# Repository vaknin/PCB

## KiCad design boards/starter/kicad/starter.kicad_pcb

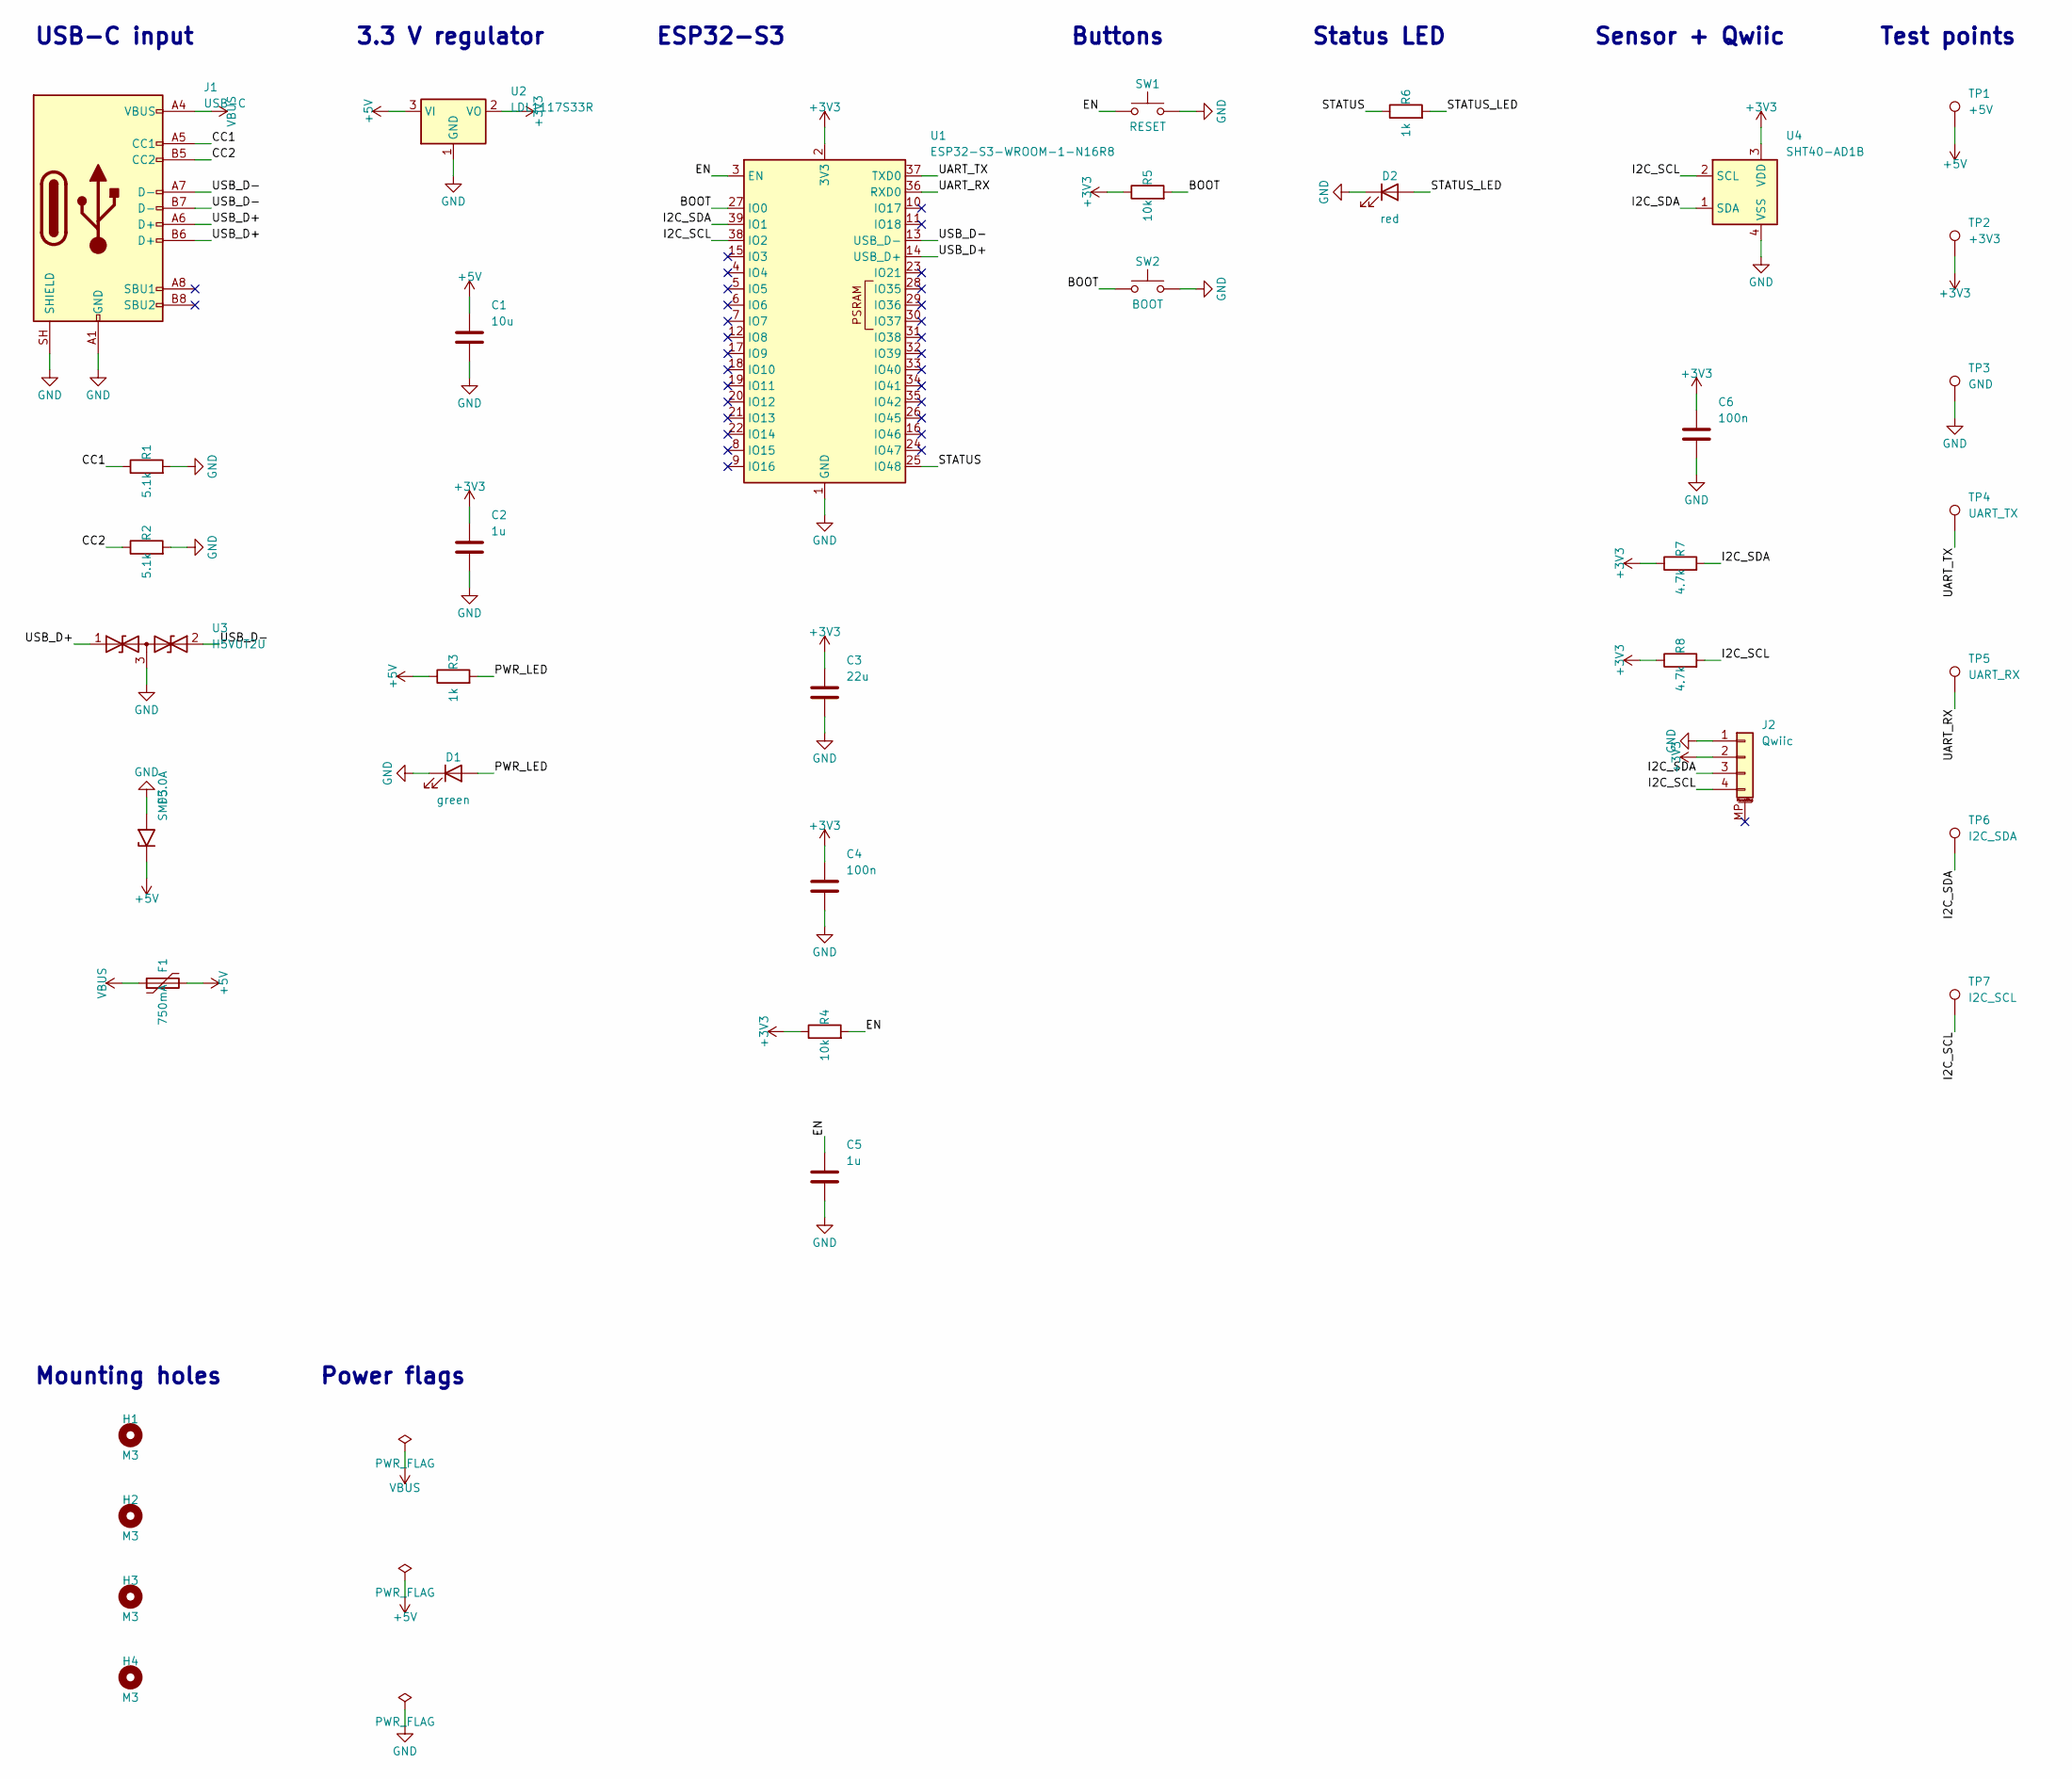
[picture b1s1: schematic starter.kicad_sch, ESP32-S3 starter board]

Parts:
C1: 10u; C_0805_2012Metric; MPN CL21A106KAYNNNE; LCSC C15850
C2, C5: 1u; C_0805_2012Metric; MPN CL21B105KBFNNNE; LCSC C28323
C3: 22u; C_0805_2012Metric; MPN CL21A226MAQNNNE; LCSC C45783
C4, C6: 100n; C_0805_2012Metric; MPN CC0805KRX7R9BB104; LCSC C49678
D1: green; LED_0805_2012Metric; MPN KT-0805G; LCSC C2297
D2: red; LED_0805_2012Metric; MPN NCD0805R1; LCSC C84256
D3: SMF5.0A; D_SOD-123F; MPN SMF5.0A; LCSC C19077497
F1: 750mA; Fuse_1206_3216Metric; MPN MF-NSMF075-2; LCSC C89653
H1, H2, H3, H4: M3; MountingHole_3.2mm_M3
J1: USB-C; USB_C_Receptacle_HRO_TYPE-C-31-M-12; MPN TYPE-C-31-M-12; LCSC C165948
J2: Qwiic; JST_SH_SM04B-SRSS-TB_1x04-1MP_P1.00mm_Horizontal; MPN SM04B-SRSS-TB; LCSC C160404
R1, R2: 5.1k; R_0805_2012Metric; MPN 0805W8F5101T5E; LCSC C27834
R3, R6: 1k; R_0805_2012Metric; MPN 0805W8F1001T5E; LCSC C17513
R4, R5: 10k; R_0805_2012Metric; MPN 0805W8F1002T5E; LCSC C17414
R7, R8: 4.7k; R_0805_2012Metric; MPN 0805W8F4701T5E; LCSC C17673
SW1: RESET; SW_Push_1P1T_XKB_TS-1187A; MPN TS-1187A-B-A-B; LCSC C318884
SW2: BOOT; SW_Push_1P1T_XKB_TS-1187A; MPN TS-1187A-B-A-B; LCSC C318884
TP1: +5V; TestPoint_Pad_D1.5mm
TP2: +3V3; TestPoint_Pad_D1.5mm
TP3: GND; TestPoint_Pad_D1.5mm
TP4: UART_TX; TestPoint_Pad_D1.5mm
TP5: UART_RX; TestPoint_Pad_D1.5mm
TP6: I2C_SDA; TestPoint_Pad_D1.5mm
TP7: I2C_SCL; TestPoint_Pad_D1.5mm
U1: ESP32-S3-WROOM-1-N16R8; ESP32-S3-WROOM-1_EPAD-Drill0.3; MPN ESP32-S3-WROOM-1-N16R8; LCSC C2913202
U2: LDL1117S33R; SOT-223-3_TabPin2; MPN LDL1117S33R; LCSC C435835
U3: H5VUT2U; SOT-23; MPN H5VUT2U; LCSC C20615824
U4: SHT40-AD1B; Sensirion_DFN-4_1.5x1.5mm_P0.8mm_SHT4x_NoCentralPad; MPN SHT40-AD1B-R2; LCSC C2909890

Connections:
+3V3: C2.1, C3.1, C4.1, C6.1, J2.2, R4.1, R5.1, R7.1, R8.1, TP2.1, U1.2 (3V3), U2.2 (VO), U4.3 (VDD)
+5V: C1.1, D3.1 (A1), F1.2, R3.1, TP1.1, U2.3 (VI)
/BOOT: R5.2, SW2.1, U1.27 (IO0)
/CC1: J1.A5 (CC1), R1.1
/CC2: J1.B5 (CC2), R2.1
/EN: C5.1, R4.2, SW1.1, U1.3 (EN)
/I2C_SCL: J2.4, R8.2, TP7.1, U1.38 (IO2), U4.2 (SCL)
/I2C_SDA: J2.3, R7.2, TP6.1, U1.39 (IO1), U4.1 (SDA)
/PWR_LED: D1.2 (A), R3.2
/STATUS: R6.1, U1.25 (IO48)
/STATUS_LED: D2.2 (A), R6.2
/UART_RX: TP5.1, U1.36 (RXD0)
/UART_TX: TP4.1, U1.37 (TXD0)
/USB_D+: J1.A6 (D+), J1.B6 (D+), U1.14 (USB_D+), U3.1 (A1)
/USB_D-: J1.A7 (D-), J1.B7 (D-), U1.13 (USB_D-), U3.2 (A2)
GND: C1.2, C2.2, C3.2, C4.2, C5.2, C6.2, D1.1 (K), D2.1 (K), D3.2 (A2), J1.A1 (GND), J1.A12 (GND), J1.B1 (GND), J1.B12 (GND), J1.SH (SHIELD), J2.1, R1.2, R2.2, SW1.2, SW2.2, TP3.1, U1.1 (GND), U1.40 (GND), U1.41 (GND), U2.1 (GND), U3.3 (common), U4.4 (VSS)
VBUS: F1.1, J1.A4 (VBUS), J1.A9 (VBUS), J1.B4 (VBUS), J1.B9 (VBUS)

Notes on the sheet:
Mounting holes
Sensor + Qwiic
ESP32-S3
USB-C input
Power flags
Buttons
Test points
3.3 V regulator
Status LED

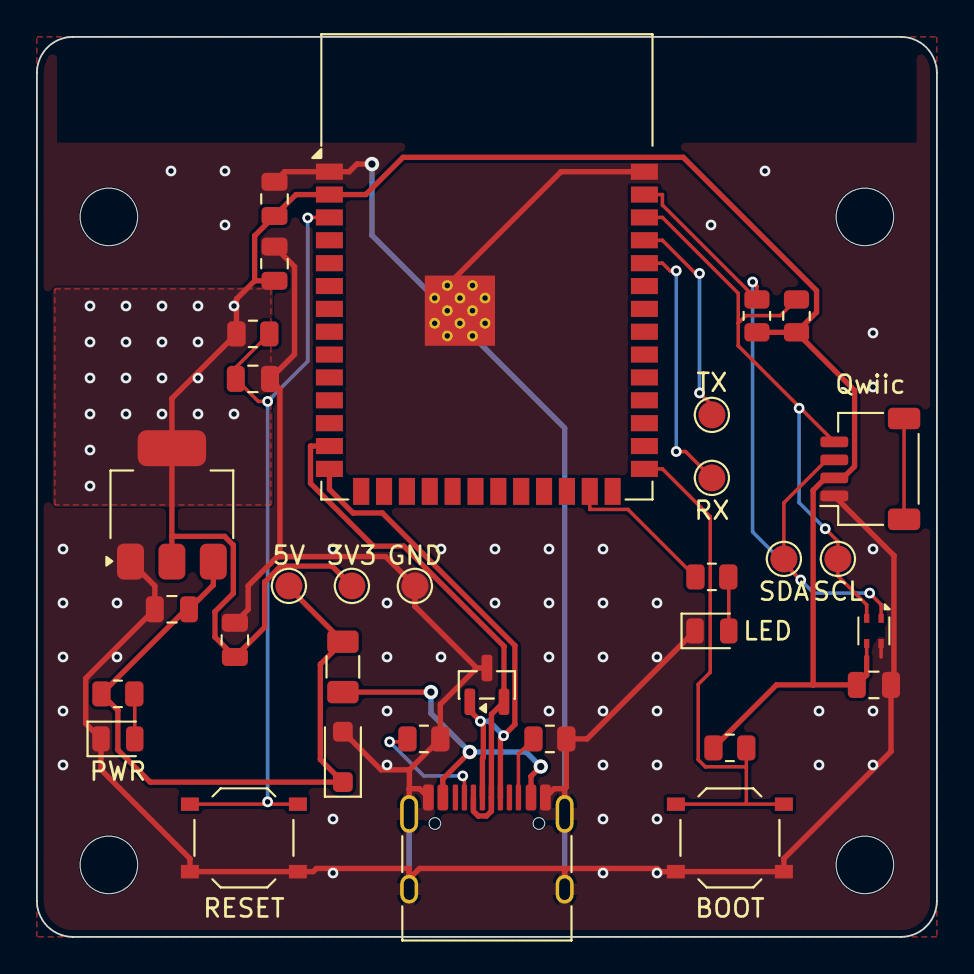
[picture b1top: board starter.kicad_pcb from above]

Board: 2 copper layers, 50.0 x 50.0 mm, 37 parts (0 on the bottom side), 17 nets.

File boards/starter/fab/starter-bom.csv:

Comment,Designator,Footprint,LCSC
10u,C1,C_0805_2012Metric,C15850
1u,"C2,C5",C_0805_2012Metric,C28323
22u,C3,C_0805_2012Metric,C45783
100n,"C4,C6",C_0805_2012Metric,C49678
green,D1,LED_0805_2012Metric,C2297
red,D2,LED_0805_2012Metric,C84256
SMF5.0A,D3,D_SOD-123F,C19077497
750mA,F1,Fuse_1206_3216Metric,C89653
USB-C,J1,USB_C_Receptacle_HRO_TYPE-C-31-M-12,C165948
Qwiic,J2,JST_SH_SM04B-SRSS-TB_1x04-1MP_P1.00mm_Horizontal,C160404
5.1k,"R1,R2",R_0805_2012Metric,C27834
1k,"R3,R6",R_0805_2012Metric,C17513
10k,"R4,R5",R_0805_2012Metric,C17414
4.7k,"R7,R8",R_0805_2012Metric,C17673
RESET,SW1,SW_Push_1P1T_XKB_TS-1187A,C318884
BOOT,SW2,SW_Push_1P1T_XKB_TS-1187A,C318884
ESP32-S3-WROOM-1-N16R8,U1,ESP32-S3-WROOM-1_EPAD-Drill0.3,C2913202
LDL1117S33R,U2,SOT-223-3_TabPin2,C435835
H5VUT2U,U3,SOT-23,C20615824
SHT40-AD1B,U4,Sensirion_DFN-4_1.5x1.5mm_P0.8mm_SHT4x_NoCentralPad,C2909890

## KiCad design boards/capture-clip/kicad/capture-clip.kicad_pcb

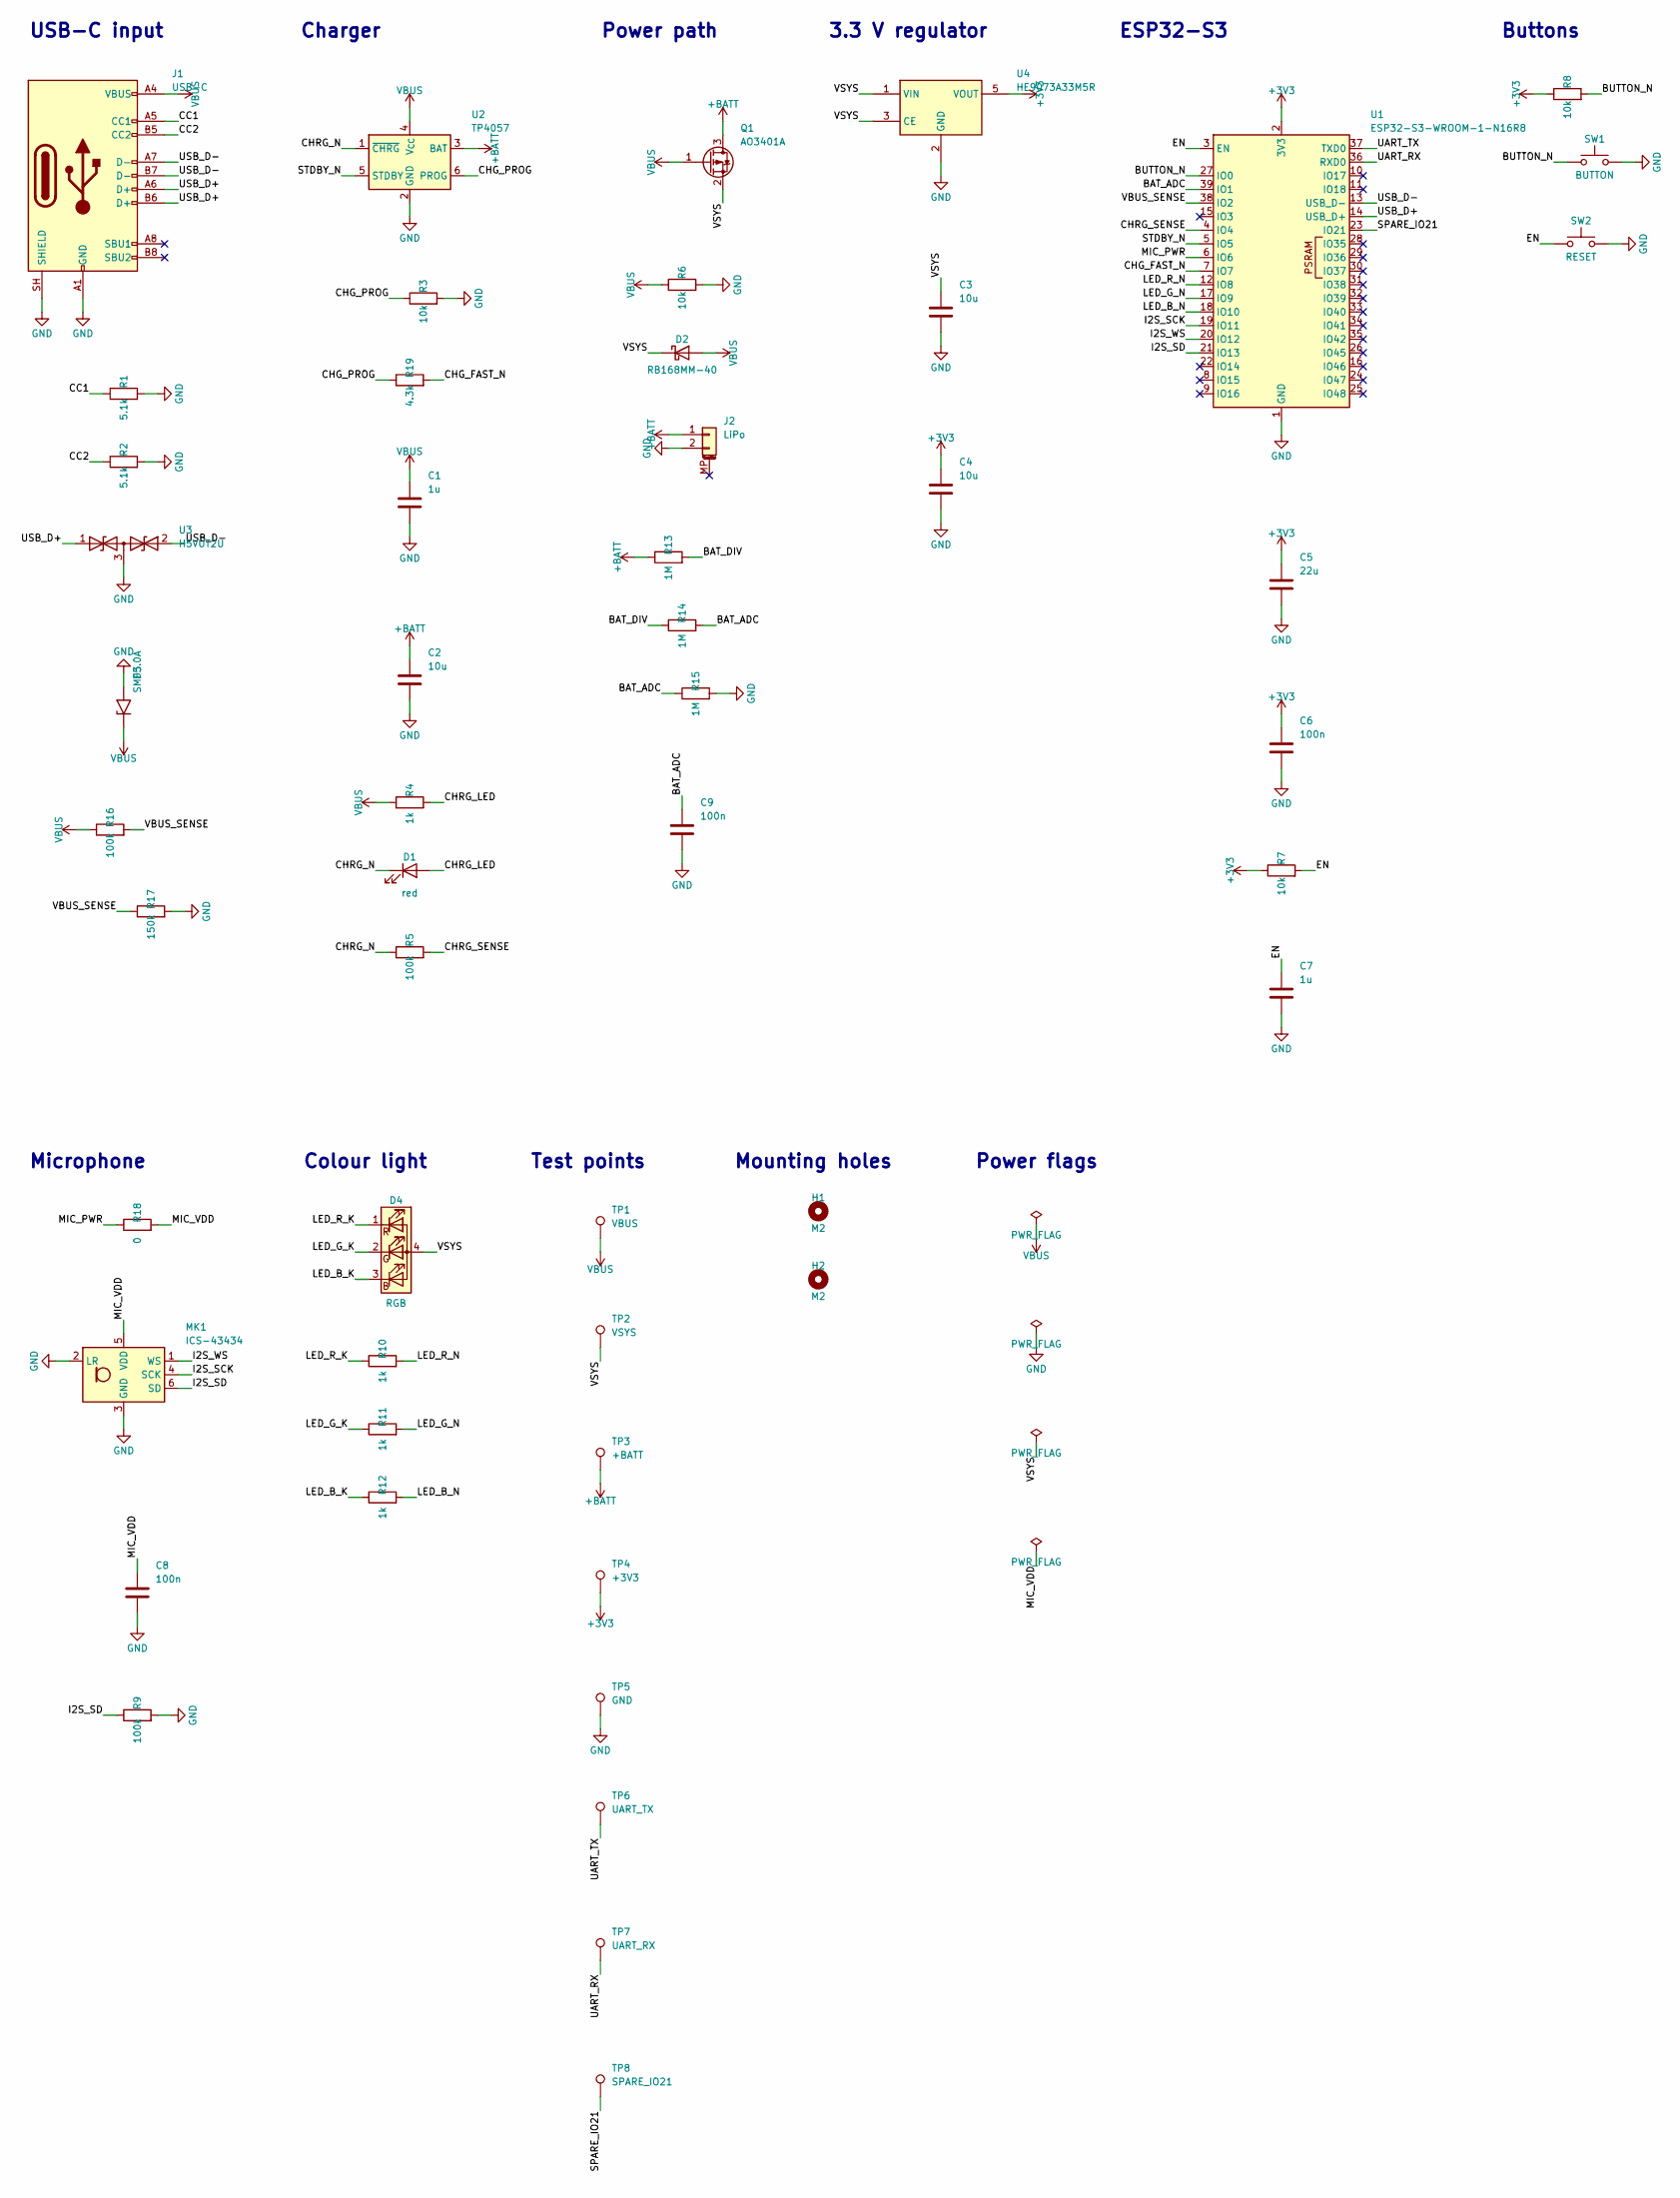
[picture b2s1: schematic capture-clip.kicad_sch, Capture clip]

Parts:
C1, C7: 1u; C_0805_2012Metric; LCSC C28323
C2, C3, C4: 10u; C_0805_2012Metric; LCSC C15850
C5: 22u; C_0805_2012Metric; LCSC C45783
C6, C8, C9: 100n; C_0805_2012Metric; LCSC C49678
D1: red; LED_0805_2012Metric; LCSC C84256
D2: RB168MM-40; D_SOD-123F; MPN RB168MM-40TR; LCSC C509936
D3: SMF5.0A; D_SOD-123F; MPN SMF5.0A; LCSC C19077497
D4: RGB; LED_LiteOn_LTST-C19HE1WT; MPN LTST-C19HE1WT; LCSC C458749
H1, H2: M2; MountingHole_2.5mm
J1: USB-C; USB_C_Receptacle_HRO_TYPE-C-31-M-12; MPN TYPE-C-31-M-12; LCSC C165948
J2: LiPo; JST_PH_S2B-PH-SM4-TB_1x02-1MP_P2.00mm_Horizontal; MPN S2B-PH-SM4-TB(LF)(SN); LCSC C295747
MK1: ICS-43434; InvenSense_ICS-43434-6_3.5x2.65mm; MPN ICS-43434; LCSC C5656610
Q1: AO3401A; SOT-23; MPN AO3401A; LCSC C15127
R1, R2: 5.1k; R_0805_2012Metric; LCSC C27834
R3, R6, R7, R8: 10k; R_0805_2012Metric; LCSC C17414
R4, R10, R11, R12: 1k; R_0805_2012Metric; LCSC C17513
R5, R9, R16: 100k; R_0805_2012Metric; LCSC C149504
R13, R14, R15: 1M; R_0805_2012Metric; LCSC C17514
R17: 150k; R_0805_2012Metric; LCSC C17470
R18: 0; R_0805_2012Metric; LCSC C17477
R19: 4.3k; R_0805_2012Metric; LCSC C17667
SW1: BUTTON; SW_Push_1TS009xxxx-xxxx-xxxx_6x6x5mm; MPN 1TS009A-1800-5000-CT; LCSC C319409
SW2: RESET; SW_SPST_TS-1088-xR020; MPN TS-1088-AR02016; LCSC C720477
TP1: VBUS; TestPoint_Pad_D1.5mm
TP2: VSYS; TestPoint_Pad_D1.5mm
TP3: +BATT; TestPoint_Pad_D1.5mm
TP4: +3V3; TestPoint_Pad_D1.5mm
TP5: GND; TestPoint_Pad_D1.5mm
TP6: UART_TX; TestPoint_Pad_D1.5mm
TP7: UART_RX; TestPoint_Pad_D1.5mm
TP8: SPARE_IO21; TestPoint_Pad_D1.5mm
U1: ESP32-S3-WROOM-1-N16R8; ESP32-S3-WROOM-1_EPAD-Drill0.3; MPN ESP32-S3-WROOM-1-N16R8; LCSC C2913202
U2: TP4057; SOT-23-6; MPN TP4057-42-SOT26-R; LCSC C12044
U3: H5VUT2U; SOT-23; MPN H5VUT2U; LCSC C20615824
U4: HE9073A33M5R; SOT-23-5; MPN HE9073A33M5R; LCSC C723789

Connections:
+3V3: C4.1, C5.1, C6.1, R7.1, R8.1, TP4.1, U1.2 (3V3), U4.5 (VOUT)
+BATT: C2.1, J2.1, Q1.3 (D), R13.1, TP3.1, U2.3 (BAT)
/BAT_ADC: C9.1, R14.2, R15.1, U1.39 (IO1)
/BAT_DIV: R13.2, R14.1
/BUTTON_N: R8.2, SW1.1, U1.27 (IO0)
/CC1: J1.A5 (CC1), R1.1
/CC2: J1.B5 (CC2), R2.1
/CHG_FAST_N: R19.2, U1.7 (IO7)
/CHG_PROG: R3.1, R19.1, U2.6 (PROG)
/CHRG_LED: D1.2 (A), R4.2
/CHRG_N: D1.1 (K), R5.1, U2.1 (~CHRG)
/CHRG_SENSE: R5.2, U1.4 (IO4)
/EN: C7.1, R7.2, SW2.1, U1.3 (EN)
/I2S_SCK: MK1.4 (SCK), U1.19 (IO11)
/I2S_SD: MK1.6 (SD), R9.1, U1.21 (IO13)
/I2S_WS: MK1.1 (WS), U1.20 (IO12)
/LED_B_K: D4.3 (BK), R12.1
/LED_B_N: R12.2, U1.18 (IO10)
/LED_G_K: D4.2 (GK), R11.1
/LED_G_N: R11.2, U1.17 (IO9)
/LED_R_K: D4.1 (RK), R10.1
/LED_R_N: R10.2, U1.12 (IO8)
/MIC_PWR: R18.1, U1.6 (IO6)
/MIC_VDD: C8.1, MK1.5 (VDD), R18.2
/SPARE_IO21: TP8.1, U1.23 (IO21)
/STDBY_N: U1.5 (IO5), U2.5 (STDBY)
/UART_RX: TP7.1, U1.36 (RXD0)
/UART_TX: TP6.1, U1.37 (TXD0)
/USB_D+: J1.A6 (D+), J1.B6 (D+), U1.14 (USB_D+), U3.1 (A1)
/USB_D-: J1.A7 (D-), J1.B7 (D-), U1.13 (USB_D-), U3.2 (A2)
/VBUS_SENSE: R16.2, R17.1, U1.38 (IO2)
/VSYS: C3.1, D2.1 (K), D4.4 (A), Q1.2 (S), TP2.1, U4.1 (VIN), U4.3 (CE)
GND: C1.2, C2.2, C3.2, C4.2, C5.2, C6.2, C7.2, C8.2, C9.2, D3.2 (A2), J1.A1 (GND), J1.A12 (GND), J1.B1 (GND), J1.B12 (GND), J1.SH (SHIELD), J2.2, MK1.2 (LR), MK1.3 (GND), R1.2, R2.2, R3.2, R6.2, R9.2, R15.2, R17.2, SW1.2, SW2.2, TP5.1, U1.1 (GND), U1.40 (GND), U1.41 (GND), U2.2 (GND), U3.3 (common), U4.2 (GND)
VBUS: C1.1, D2.2 (A), D3.1 (A1), J1.A4 (VBUS), J1.A9 (VBUS), J1.B4 (VBUS), J1.B9 (VBUS), Q1.1 (G), R4.1, R6.1, R16.1, TP1.1, U2.4 (V_{CC})

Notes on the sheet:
Test points
Power path
Colour light
3.3 V regulator
Buttons
Power flags
USB-C input
Charger
Mounting holes
Microphone
ESP32-S3

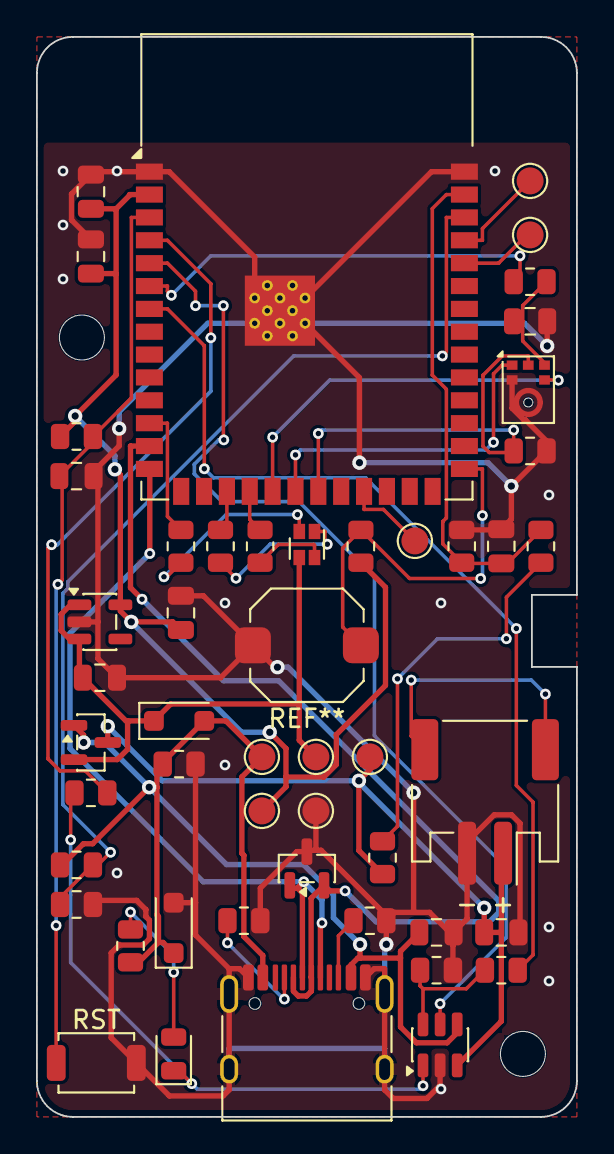
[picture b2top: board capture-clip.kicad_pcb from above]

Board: 2 copper layers, 30.0 x 60.0 mm, 52 parts (0 on the bottom side), 34 nets.

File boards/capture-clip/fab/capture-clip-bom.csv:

Comment,Designator,Footprint,LCSC
1u,"C1,C7",C_0805_2012Metric,C28323
10u,"C2,C3,C4",C_0805_2012Metric,C15850
22u,C5,C_0805_2012Metric,C45783
100n,"C6,C8,C9",C_0805_2012Metric,C49678
red,D1,LED_0805_2012Metric,C84256
RB168MM-40,D2,D_SOD-123F,C509936
SMF5.0A,D3,D_SOD-123F,C19077497
RGB,D4,LED_LiteOn_LTST-C19HE1WT,C458749
USB-C,J1,USB_C_Receptacle_HRO_TYPE-C-31-M-12,C165948
LiPo,J2,JST_PH_S2B-PH-SM4-TB_1x02-1MP_P2.00mm_Horizontal,C295747
ICS-43434,MK1,InvenSense_ICS-43434-6_3.5x2.65mm,C5656610
AO3401A,Q1,SOT-23,C15127
5.1k,"R1,R2",R_0805_2012Metric,C27834
1M,"R13,R14,R15",R_0805_2012Metric,C17514
100k,"R5,R9,R16",R_0805_2012Metric,C149504
150k,R17,R_0805_2012Metric,C17470
0,R18,R_0805_2012Metric,C17477
4.3k,R19,R_0805_2012Metric,C17667
10k,"R3,R6,R7,R8",R_0805_2012Metric,C17414
1k,"R4,R10,R11,R12",R_0805_2012Metric,C17513
BUTTON,SW1,SW_Push_1TS009xxxx-xxxx-xxxx_6x6x5mm,C319409
RESET,SW2,SW_SPST_TS-1088-xR020,C720477
ESP32-S3-WROOM-1-N16R8,U1,ESP32-S3-WROOM-1_EPAD-Drill0.3,C2913202
TP4057,U2,SOT-23-6,C12044
H5VUT2U,U3,SOT-23,C20615824
HE9073A33M5R,U4,SOT-23-5,C723789

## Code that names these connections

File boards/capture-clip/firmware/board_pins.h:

// Generated by pcbgen from board.toml; do not edit. Regenerate with the `fw` stage.
#pragma once

#include "driver/gpio.h"

#define BOARD_NAME "capture-clip"
#define BOARD_REVISION "A"

// BUTTON: module pin IO0, net BUTTON_N, in, active low; main button SW1 to GND, 10k pull-up (R8); deep-sleep wake (ext1, any low); strapping pin: held low at a full reset = download mode
#define PIN_BUTTON GPIO_NUM_0
#define PIN_BUTTON_ACTIVE_LOW 1

// BAT_ADC: module pin IO1, net BAT_ADC, in; cell voltage / 3 (R13 + R14 over R15, 100n C9); ADC1_CH0 at 6 dB; read at rest, averaged
#define PIN_BAT_ADC GPIO_NUM_1

// VBUS_SENSE: module pin IO2, net VBUS_SENSE, in; USB 5 V x 0.6 (R16 100k over R17 150k): high = USB present; deep-sleep wake (ext0, high)
#define PIN_VBUS_SENSE GPIO_NUM_2

// CHRG: module pin IO4, net CHRG_SENSE, in, active low; TP4057 CHRG (open drain, low while charging) through 100k (R5); never an internal pull-up (a low would read as ~2.4 V); the charge light pulls it high
#define PIN_CHRG GPIO_NUM_4
#define PIN_CHRG_ACTIVE_LOW 1

// STDBY: module pin IO5, net STDBY_N, in, active low; TP4057 STDBY (open drain, low when the charge is complete); internal pull-up only while VBUS_SENSE is high, off before sleep
#define PIN_STDBY GPIO_NUM_5
#define PIN_STDBY_ACTIVE_LOW 1

// MIC_PWR: module pin IO6, net MIC_PWR, out; the microphone's VDD through R18 (0 ohm), about 0.5 mA; high = on; stop and ground SCK/WS before switching it off; held low in sleep
#define PIN_MIC_PWR GPIO_NUM_6

// CHG_FAST: module pin IO7, net CHG_FAST_N, out, active low; fast charge: open drain; low = R19 (4.3k) in parallel with R3 on the TP4057's PROG = ~333 mA; released (hi-Z) = 100 mA. Never driven high, no pulls. Released whenever Wi-Fi is on, asleep and at reset
#define PIN_CHG_FAST GPIO_NUM_7
#define PIN_CHG_FAST_ACTIVE_LOW 1

// LED_R: module pin IO8, net LED_R_N, out, active low; red cathode of D4 through 1k (R10); anode on VSYS; low = on; held high in sleep
#define PIN_LED_R GPIO_NUM_8
#define PIN_LED_R_ACTIVE_LOW 1

// LED_G: module pin IO9, net LED_G_N, out, active low; green cathode of D4 through 1k (R11); low = on; held high in sleep
#define PIN_LED_G GPIO_NUM_9
#define PIN_LED_G_ACTIVE_LOW 1

// LED_B: module pin IO10, net LED_B_N, out, active low; blue cathode of D4 through 1k (R12); low = on; held high in sleep
#define PIN_LED_B GPIO_NUM_10
#define PIN_LED_B_ACTIVE_LOW 1

// I2S_SCK: module pin IO11, net I2S_SCK, out; microphone bit clock (1.024 MHz at 16 kHz); held low in sleep
#define PIN_I2S_SCK GPIO_NUM_11

// I2S_WS: module pin IO12, net I2S_WS, out; microphone word select; the mic is the left channel (LR to GND); held low in sleep
#define PIN_I2S_WS GPIO_NUM_12

// I2S_SD: module pin IO13, net I2S_SD, in; microphone data; 100k pull-down (R9)
#define PIN_I2S_SD GPIO_NUM_13

// SPARE_IO21: module pin IO21, net SPARE_IO21, io; spare, on test point TP8 (rework)
#define PIN_SPARE_IO21 GPIO_NUM_21

// UART_TX: module pin TXD0, net UART_TX, out; test point TP6; boot log
#define PIN_UART_TX GPIO_NUM_43

// UART_RX: module pin RXD0, net UART_RX, in; test point TP7
#define PIN_UART_RX GPIO_NUM_44

// USB_DM: module pin USB_D-, net USB_D-, io; native USB (flashing, serial console, provisioning)
#define PIN_USB_DM GPIO_NUM_19

// USB_DP: module pin USB_D+, net USB_D+, io; native USB (flashing, serial console, provisioning)
#define PIN_USB_DP GPIO_NUM_20

// Self-tests the firmware runs at bring-up: static const char *t[] = BOARD_SELF_TESTS;
#define BOARD_SELF_TEST_COUNT 6
#define BOARD_SELF_TESTS {"mic", "led_rgb", "button", "battery", "usb_sense", "wifi"}

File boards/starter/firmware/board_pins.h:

// Generated by pcbgen from board.toml; do not edit. Regenerate with the `fw` stage.
#pragma once

#include "driver/gpio.h"

#define BOARD_NAME "starter"
#define BOARD_REVISION "0"

// I2C_SDA: module pin IO1, net I2C_SDA, io; SHT40 at 0x44 and the Qwiic port; 4.7k pull-up (R7)
#define PIN_I2C_SDA GPIO_NUM_1

// I2C_SCL: module pin IO2, net I2C_SCL, out; 4.7k pull-up (R8)
#define PIN_I2C_SCL GPIO_NUM_2

// STATUS_LED: module pin IO48, net STATUS, out; red LED D2 through 1k (R6); high = on
#define PIN_STATUS_LED GPIO_NUM_48

// BOOT: module pin IO0, net BOOT, in, active low; BOOT button SW2, 10k pull-up (R5); strapping pin: held low at reset = download mode
#define PIN_BOOT GPIO_NUM_0
#define PIN_BOOT_ACTIVE_LOW 1

// UART_TX: module pin TXD0, net UART_TX, out; test point TP4; boot log
#define PIN_UART_TX GPIO_NUM_43

// UART_RX: module pin RXD0, net UART_RX, in; test point TP5
#define PIN_UART_RX GPIO_NUM_44

// USB_DM: module pin USB_D-, net USB_D-, io; native USB (flashing and serial console)
#define PIN_USB_DM GPIO_NUM_19

// USB_DP: module pin USB_D+, net USB_D+, io; native USB (flashing and serial console)
#define PIN_USB_DP GPIO_NUM_20

// Self-tests the firmware runs at bring-up: static const char *t[] = BOARD_SELF_TESTS;
#define BOARD_SELF_TEST_COUNT 4
#define BOARD_SELF_TESTS {"sht40", "i2c_scan", "status_led", "boot_button"}
